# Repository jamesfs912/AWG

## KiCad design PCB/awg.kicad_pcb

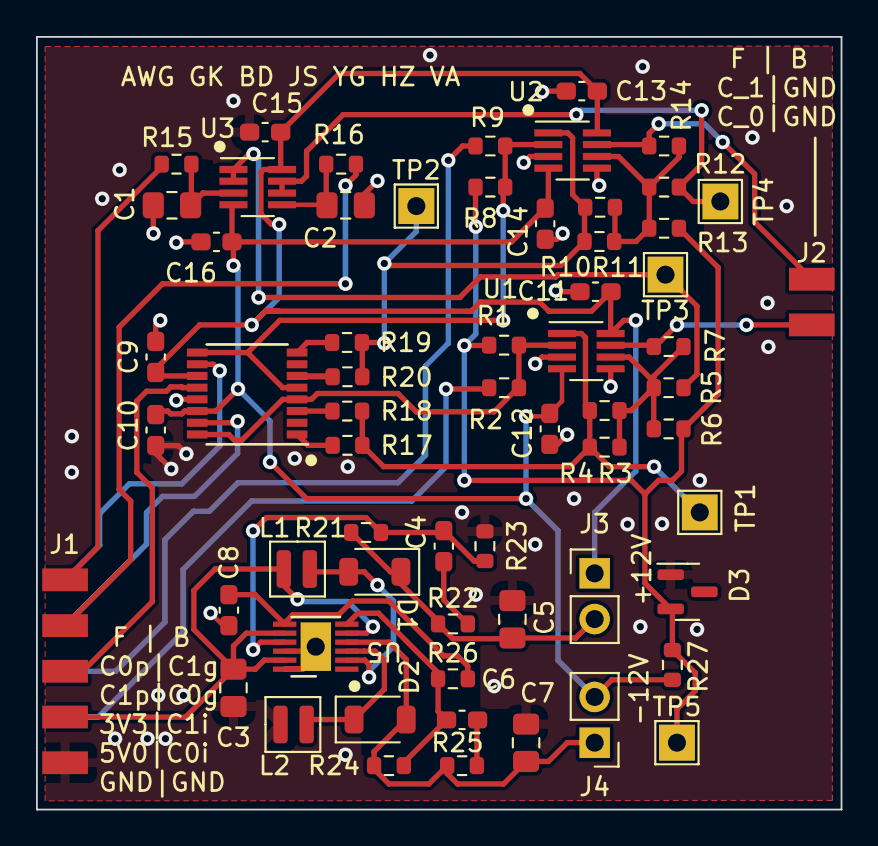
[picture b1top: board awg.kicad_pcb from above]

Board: 2 copper layers, 44.7 x 42.9 mm, 62 parts (0 on the bottom side), 37 nets.

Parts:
C1, C2, C3, C5, C7: 10u; C_0805_2012Metric_Pad1.18x1.45mm_HandSolder
C4, C6: 120p; C_0603_1608Metric_Pad1.08x0.95mm_HandSolder
C8, C9, C10, C11, C12, C13, C14, C15, C16: 100n; C_0603_1608Metric_Pad1.08x0.95mm_HandSolder
D1, D2: S14
D3: LM4040-5; SOT-23
J1: 02x05; 2x05
J2: 02x02; 2x02
J3, J4: 01x02; PinHeader_1x02_P2.54mm_Vertical
L1, L2: 4.7u; NRH2410
R1, R3, R4, R6, R7, R8, R10, R11, R13, R14, R18, R20, R23, R26: 10K; R_0603_1608Metric
R2, R5, R9, R12: 3K3; R_0603_1608Metric
R15, R16, R17, R19, R22, R25, R27: 1K; R_0603_1608Metric
R21: 110k; R_0603_1608Metric
R24: 100k; R_0603_1608Metric
TP1, TP2, TP3, TP4, TP5: TestPoint; TestPoint_THTPad_2.0x2.0mm_Drill1.0mm
U1, U2, U3: LM2904; SOT-23-8_Handsoldering
U4: DG403; TSSOP-16-1EP_4.4x5mm_P0.65mm
U5: r1283; DFN-12

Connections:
+3.3V: J1.3, U4.12 (VL)
+5V: C3.1, J1.4, L1.1, U5.5 (CE), U5.8 (Vcc), U5.11 (PVcc)
+12V: C9.2, C11.1, C13.1, C15.1, J3.1, U1.8 (V+), U2.8 (V+), U3.8 (V+), U4.11 (V+)
-5V: D3.2 (A), R1.1, R6.2, R8.1, R13.2, R27.1, TP5.1
-12V: C10.2, C12.2, C14.2, C16.2, J4.2, R27.2, U1.4 (V-), U2.4 (V-), U3.4 (V-), U4.14 (V-)
/C0_FB: R1.2, R2.2, U1.2 (-), U4.4 (S3), U4.16 (S1)
/C0_IN: J1.9, R2.1
/C0_OUT_G: R3.2, R4.1, R17.2, R18.1, TP1.1, U1.1
/C0_OUT_GO: J2.2, R7.2, U1.7
/C0_PWM_OFF: J1.1, R15.1
/C0_S_GAIN: J1.7, U4.15 (IN1)
/C0_V_OFF: R5.1, TP3.1, U3.1, U3.2 (-)
/C1_FB: R8.2, R9.2, U2.2 (-), U4.5 (S4), U4.9 (S2)
/C1_IN: J1.8, R9.1
/C1_OUT_G: R10.1, R11.1, R19.2, R20.2, TP2.1, U2.1
/C1_OUT_GO: J2.1, R14.2, U2.7
/C1_PWM_OFF: J1.2, R16.1
/C1_S_GAIN: J1.6, U4.10 (IN2)
/C1_V_OFF: R12.1, TP4.1, U3.6 (-), U3.7
GND: C1.2, C2.2, C3.2, C5.2, C7.1, C8.2, C9.1, C10.1, C11.2, C12.1, C13.2, C14.1, C15.2, C16.1, D3.1 (K), J1.5, J1.10, J2.3, J2.4, L2.2, R23.1, U1.3 (+), U1.5 (+), U2.3 (+), U2.5 (+), U4.13 (GND), U5.10 (GND), U5.12 (PGND), U5.13 (GND)
unnamed: C4.1, R22.2
unnamed: C6.1, R25.2
unnamed: D1.2 (A), L1.2, U5.2 (Lx1)
unnamed: C5.1, D1.1 (K), J3.2, R21.1, R22.1
unnamed: C7.2, D2.2 (A), J4.1, R24.1, R25.1, U5.4 (Voutn)
unnamed: D2.1 (K), L2.1, U5.3 (Lx2)
unnamed: R3.1, R4.2, R5.2, R6.1, R7.1, U1.6 (-)
unnamed: R10.2, R11.2, R12.2, R13.1, R14.1, U2.6 (-)
unnamed: C1.1, R15.2, U3.3 (+)
unnamed: C2.1, R16.2, U3.5 (+)
unnamed: R17.1, U4.1 (D1)
unnamed: R19.1, U4.8 (D2)
unnamed: R18.2, U4.3 (D3)
unnamed: R20.1, U4.6 (D4)
unnamed: C4.2, R21.2, R23.2, U5.9 (Vfb1)
unnamed: C6.2, R24.2, R26.1, U5.6 (Vfb2)
unnamed: C8.1, R26.2, U5.7 (Vref)

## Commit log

2023-02-26 Add files via upload
    Python programs that create various waveforms plus a hand drawn user defined waveform using the matlab library. All .py files produce two csv files, one is a graphical representation of the wave with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
2023-02-26 Add files via upload
    Ok since I am programming the MCU I wrote some python programs for sine, triangle, square, sawtooth waveforms and a hand drawn user defined waveform. When you run the specific .py file the output pro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
2023-02-27 Add files via upload
    basic gui with amp, offset and freq. arbitrary freq doesn't work
2023-03-04 Add files via upload
    AWG and oscilloscope
2023-03-29 Created test file
2023-04-02 Text boxes + Auto scalling graphs
2023-04-02 Removed test file
2023-04-06 Create MCU Prog
2023-04-23 Create design
2023-04-23 Added PCB
2023-06-14 git is being funky
2023-06-14 Added package downloader
2023-06-15 Unit conversion complete + misc bug fixes
2023-06-15 Patched out suffixes for amplitude
2023-09-11 Documentation start
2023-09-11 Fixed offset bug
2023-09-14 9/14/23
2023-09-20 Visual Toggle Start
2023-09-20 Toggle start
2023-09-25 GUI Update requests complete
2023-10-02 Final visual GUI update
2023-10-04 PCB rev2
2023-10-04 PCB rev2 forgot stuff
2023-10-04 Window resizing
2023-10-05 moved wave gen to wavegen.py added connection.py for future stuff with handling the MCU connection, can't test cuz no board added status label and connect button, basic integration with connection.py
2023-10-07 work on connection.py
2023-10-08 Added more prefix functionality (Untested)
2023-10-08 Added requested prefix expansion
2023-10-08 Fixed amplitude bug
2023-10-09 connection.py, guide lines on graph
2023-10-09 mcu work
2023-10-09 Fixed amplitude/offset verification
2023-10-13 channel 1/2 on for dac
2023-10-13 dac channel_1/2 on
2023-10-15 removed LCD, fixed disconnect bug
2023-10-18 test scripts, auto connect
2023-10-20 dc voltage update
2023-10-24 merged wavedrawer from Vik
2023-10-26 improved conn
2023-10-28 win and mac installer added to GUI dir
2023-10-28 windows installer added
2023-10-28 mac pkg installer
2023-10-28 updated win-installer
2023-10-28 win-installer with packages
2023-10-28 added executable with packages modification done
2023-10-28 added new directories
2023-10-28 new dir for macos
2023-10-28 mac exe added with new dir
2023-10-28 added mac .app and organized dir
2023-10-28 removed unness file
2023-10-28 removed junk files from macos
2023-10-28 refactor
2023-10-29 removed commented out code, unified make exe
2023-10-30 refactor, channal class, better input
2023-10-31 fix connection, sending phase, setting phase
2023-11-02 Arb dropdown added
2023-11-03 Add files via upload
    AW class and text file for storing Arbitrary waves.
2023-11-03 Update wave_drawer.py
    add/delete waveforms.
    Fixing out of bounds errors
2023-11-03 Update channal.py
    arb wave dropdown set from saved.txt
2023-11-04 11/3
2023-11-06 11/5
2023-11-06 add theme dropdown for light/dark mode
2023-11-06 added default mode
2023-11-06 fixed mode name
2023-11-06 refactor for synchronization part 1
2023-11-07 syncronization part 2
2023-11-07 11/7
2023-11-11 added functionality to open drawer
2023-11-11 fixed dumb error for creat_file
2023-11-12 arb wave drawer, icons, still needs to send arb wave to conn
2023-11-12 all should work
2023-11-13 Documented wave_drawer.py
2023-11-22 Added documentation to majority of functions.
2023-11-22 STEM spelling moment
2023-11-22 Input_field_doc.txt added for documentation
2023-11-26 docs part 2
2023-11-27 phase fixxed hopefully
